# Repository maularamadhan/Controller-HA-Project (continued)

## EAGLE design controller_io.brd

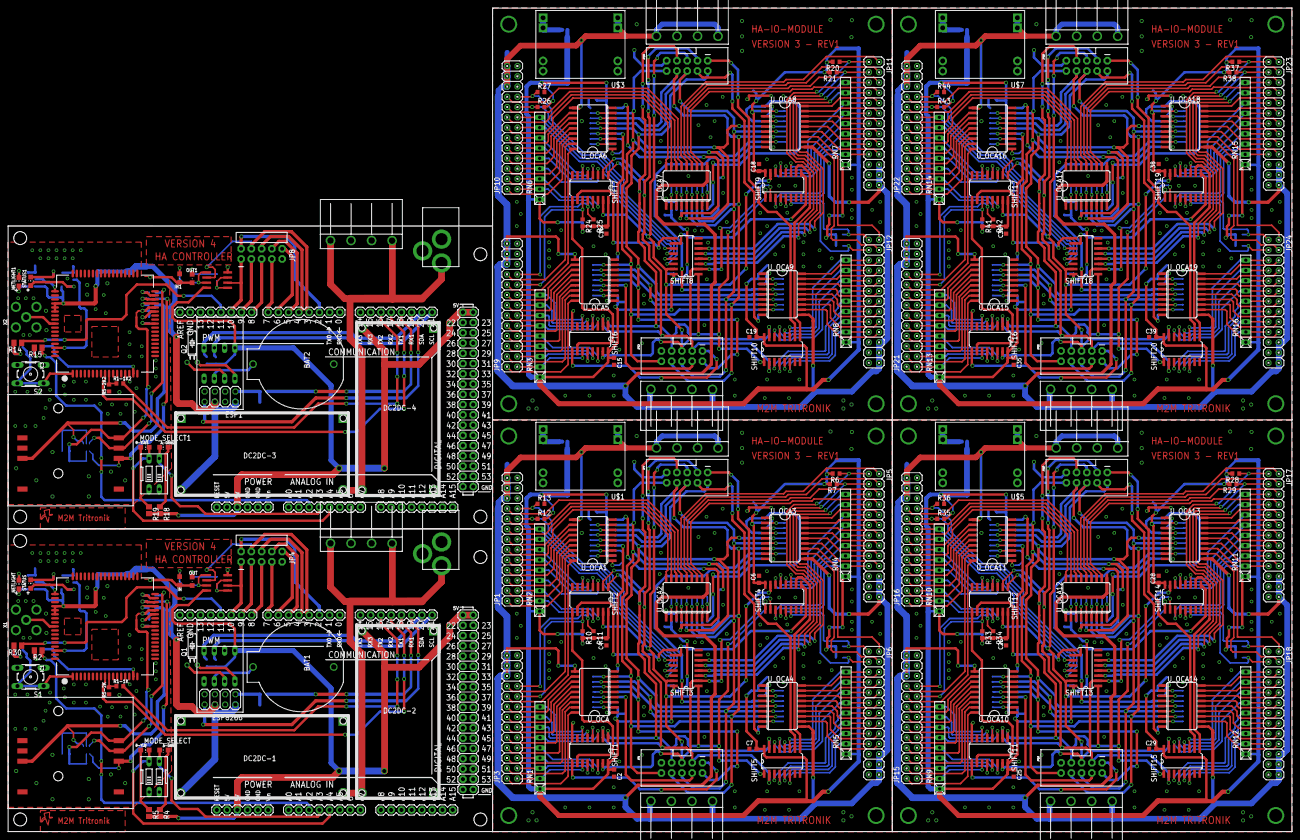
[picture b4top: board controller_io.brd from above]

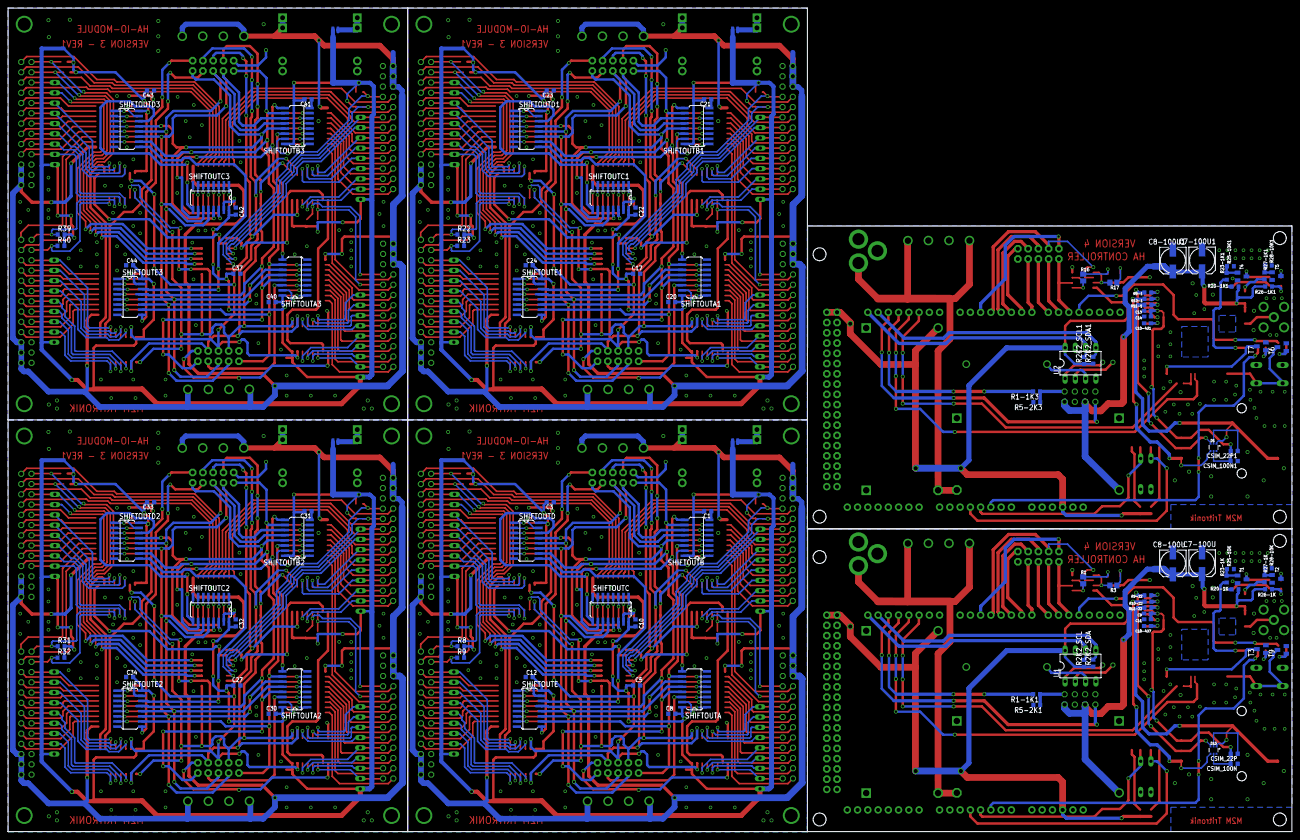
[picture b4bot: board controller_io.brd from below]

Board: 2 copper layers, 318.0 x 204.0 mm, 298 parts (112 on the bottom side), 682 nets.

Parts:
4-WAY_L-TERMINAL, 4-WAY_L-TERMINAL1: 4-PIN-CON-1759017
A-GRN, A-GRN1: green; CHIP-LED0805
ARDUINO_FOOTPRINT, ARDUINO_FOOTPRINT1: ARDUINO-MEGAFULL; ARDUINO_MEGA
B-YLW, B-YLW1: yellow; CHIP-LED0805
BAT1, BAT2: BATTCOM_20MM_PTH
C1, C2, C3, C4, C5, C6, C7, C8, C10, C12, C15, C16, C17, C18, C19, C20, C21, C22, C23, C24, C25, C26, C27, C28, C29, C30, C31, C32, C33, C34, C35, C36, C37, C38, C39, C40, C41, C42, C43, C44: 100nF; C0603K
C7-100U, C7-100U1, C8-100U, C8-100U1: 100uF; 153CLV-0605
C9, C13: 100nF; C0603
C10-4U1, C10-4U7: 4.7nF; C0603
C11, C14: 22pF; C0603
CSIM_22P, CSIM_22P1: 22pF; C0603K
CSIM_100N, CSIM_100N1: 100nF; C0603K
D1, D15: SOT363
DC2DC-1, DC2DC-2, DC2DC-3, DC2DC-4: DCDCMODULE
DC_JACKTHM, DC_JACKTHM1: 2.1MMJACKTHM; PJ-102A
ESP1, ESP8266: ESP8266
IC1, IC3: SIM900_SMT
IC2, IC4: LM358MX; SO08
IN, IN1: green; CHIPLED_0805
J1, J2, J3, J4, J5, J6, J7, J8: 4-PIN-CON-1759017
JP1, JP3, JP5, JP6, JP9, JP10, JP11, JP12, JP15, JP16, JP17, JP18, JP21, JP22, JP23, JP24: 2X13
JP2, JP7, JP13, JP14, JP19, JP20, JP25, JP26: 2X5-SHROUDED
JP4, JP8: 2X5-RA
MODE_SELECT, MODE_SELECT1: EDG-02
NETLIGHT, NETLIGHT1: green; CHIP-LED0805
OUT, OUT1: green; CHIPLED_0805
Q1, Q2: TC26H
R1, R3, R16, R17: 220; R0805
R1-1K, R1-1K1, R1-1K2, R1-1K3, R20-1K, R20-1K1, R23-1K, R23-1K1, R26-1K, R26-1K1, R27-1K, R27-1K1: 1K; R0603
R2, R14, R15, R30: 120; M0805
R2K2_SCL, R2K2_SCL1, R2K2_SDA, R2K2_SDA1: 2.2K; R0603
R4, R5, R18, R19: 1K; R0805
R5-2K, R5-2K1, R5-2K2, R5-2K3: 2K; R0603
R6, R7, R8, R9, R10, R11, R12, R13, R20, R21, R22, R23, R24, R25, R25-10K, R25-10K1, R26, R27, R28, R28-10K, R28-10K1, R29, R31, R32, R33, R34, R35, R36, R37, R38, R39, R40, R41, R42, R43, R44: 10K; R0603
R9-1, R9-22, R10-1, R10-22, R11-1, R11-22: 22; R0603
RN1, RN2, RN3, RN4, RN5, RN6, RN7, RN8, RN9, RN10, RN11, RN12, RN13, RN14, RN15, RN16: 10K; RN-9
S1, S2: B3F-10XX
SHIFT1, SHIFT2, SHIFT3, SHIFT4, SHIFT5, SHIFT6, SHIFT7, SHIFT8, SHIFT9, SHIFT10, SHIFT11, SHIFT12, SHIFT13, SHIFT14, SHIFT15, SHIFT16, SHIFT17, SHIFT18, SHIFT19, SHIFT20: 74HC165D; SO16
SHIFTOUTA, SHIFTOUTA1, SHIFTOUTA2, SHIFTOUTA3: 74HC595D; SO16
SHIFTOUTB, SHIFTOUTB1, SHIFTOUTB2, SHIFTOUTB3: 74HC595D; SO16
SHIFTOUTC, SHIFTOUTC1, SHIFTOUTC2, SHIFTOUTC3: 74HC595D; SO16
SHIFTOUTD, SHIFTOUTD1, SHIFTOUTD2, SHIFTOUTD3: 74HC595D; SO16
SHIFTOUTE, SHIFTOUTE1, SHIFTOUTE2, SHIFTOUTE3: 74HC595D; SO16
SIM_HOLDER, SIM_HOLDER1: SIM_HOLDER_PUSH
STATUS, STATUS1: yellow; CHIP-LED0805
T1, T2, T3, T4, T5, T6, T7, T9: SOT23-BEC
U1, U2: DS1307; DIL08
U$1, U$3, U$5, U$7: DCDCMODULE_SMALL; DCDCMODULE-SMALL
U$2, U$4, U$6, U$8: DOUBLE_SMALL_PAD
U_OCA, U_OCA1, U_OCA2, U_OCA3, U_OCA4, U_OCA5, U_OCA6, U_OCA7, U_OCA8, U_OCA9, U_OCA10, U_OCA11, U_OCA12, U_OCA13, U_OCA14, U_OCA15, U_OCA16, U_OCA17, U_OCA18, U_OCA19: ULN2803; SO18L
X1, X2: SMA90_DIP

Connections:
1-1: JP3.1, RN1.2, SHIFT1.11
1-2: JP3.3, RN1.3, SHIFT1.12
1-3: JP3.5, RN1.4, SHIFT1.13
1-4: JP3.7, RN1.5, SHIFT1.14
1-5: JP3.9, RN1.6, SHIFT1.3
1-6: JP3.11, RN1.7, SHIFT1.4
1-7: JP3.13, RN1.8, SHIFT1.5
1-8: JP3.15, RN1.9, SHIFT1.6
1-9: JP9.1, RN3.2, SHIFT6.11
1-10: JP9.3, RN3.3, SHIFT6.12
1-11: JP9.5, RN3.4, SHIFT6.13
1-12: JP9.7, RN3.5, SHIFT6.14
1-13: JP9.11, RN3.7, SHIFT6.4
1-14: JP9.13, RN3.8, SHIFT6.5
1-15: JP9.15, RN3.9, SHIFT6.6
1-16: JP9.9, RN3.6, SHIFT6.3
1-17: JP15.1, RN9.2, SHIFT11.11
1-18: JP15.3, RN9.3, SHIFT11.12
1-19: JP15.5, RN9.4, SHIFT11.13
1-20: JP15.7, RN9.5, SHIFT11.14
1-21: JP15.11, RN9.7, SHIFT11.4
1-22: JP15.13, RN9.8, SHIFT11.5
1-23: JP15.15, RN9.9, SHIFT11.6
1-24: JP15.9, RN9.6, SHIFT11.3
1-25: JP21.1, RN13.2, SHIFT16.11
1-26: JP21.3, RN13.3, SHIFT16.12
1-27: JP21.5, RN13.4, SHIFT16.13
1-28: JP21.7, RN13.5, SHIFT16.14
1-29: JP21.11, RN13.7, SHIFT16.4
1-30: JP21.13, RN13.8, SHIFT16.5
1-31: JP21.15, RN13.9, SHIFT16.6
1-32: JP21.9, RN13.6, SHIFT16.3
2-1: JP3.17, R10.1, SHIFT2.11
2-2: JP3.19, R11.1, SHIFT2.12
2-3: JP1.1, RN2.2, SHIFT2.13
2-4: JP1.3, RN2.3, SHIFT2.14
2-5: JP1.5, RN2.4, SHIFT2.3
2-6: JP1.7, RN2.5, SHIFT2.4
2-7: JP1.9, RN2.6, SHIFT2.5
2-8: JP1.11, RN2.7, SHIFT2.6
2-9: JP9.17, R24.1, SHIFT7.11
2-10: JP9.19, R25.1, SHIFT7.12
2-11: JP10.1, RN6.2, SHIFT7.13
2-12: JP10.3, RN6.3, SHIFT7.14
2-13: JP10.5, RN6.4, SHIFT7.3
2-14: JP10.7, RN6.5, SHIFT7.4
2-15: JP10.9, RN6.6, SHIFT7.5
2-16: JP10.11, RN6.7, SHIFT7.6
2-17: JP15.17, R33.1, SHIFT12.11
2-18: JP15.19, R34.1, SHIFT12.12
2-19: JP16.1, RN10.2, SHIFT12.13
2-20: JP16.3, RN10.3, SHIFT12.14
2-21: JP16.5, RN10.4, SHIFT12.3
2-22: JP16.7, RN10.5, SHIFT12.4
2-23: JP16.9, RN10.6, SHIFT12.5
2-24: JP16.11, RN10.7, SHIFT12.6
2-25: JP21.17, R41.1, SHIFT17.11
2-26: JP21.19, R42.1, SHIFT17.12
2-27: JP22.1, RN14.2, SHIFT17.13
2-28: JP22.3, RN14.3, SHIFT17.14
2-29: JP22.5, RN14.4, SHIFT17.3
2-30: JP22.7, RN14.5, SHIFT17.4
2-31: JP22.9, RN14.6, SHIFT17.5
2-32: JP22.11, RN14.7, SHIFT17.6
3-1: JP1.13, RN2.8, SHIFT3.11
3-2: JP1.15, RN2.9, SHIFT3.12
3-3: JP1.17, R12.1, SHIFT3.13
3-4: JP1.19, R13.1, SHIFT3.14
3-5: JP5.1, R6.1, SHIFT3.3
3-6: JP5.3, R7.1, SHIFT3.4
3-7: JP5.5, RN4.9, SHIFT3.5
3-8: JP5.7, RN4.8, SHIFT3.6
3-9: JP10.13, RN6.8, SHIFT8.11
3-10: JP10.15, RN6.9, SHIFT8.12
3-11: JP10.17, R26.1, SHIFT8.13
3-12: JP10.19, R27.1, SHIFT8.14
3-13: JP11.1, R20.1, SHIFT8.3
3-14: JP11.3, R21.1, SHIFT8.4
3-15: JP11.5, RN7.9, SHIFT8.5
3-16: JP11.7, RN7.8, SHIFT8.6
3-17: JP16.13, RN10.8, SHIFT13.11
3-18: JP16.15, RN10.9, SHIFT13.12
3-19: JP16.17, R35.1, SHIFT13.13
3-20: JP16.19, R36.1, SHIFT13.14
3-21: JP17.1, R28.1, SHIFT13.3
3-22: JP17.3, R29.1, SHIFT13.4
3-23: JP17.5, RN11.9, SHIFT13.5
3-24: JP17.7, RN11.8, SHIFT13.6
3-25: JP22.13, RN14.8, SHIFT18.11
3-26: JP22.15, RN14.9, SHIFT18.12
3-27: JP22.17, R43.1, SHIFT18.13
3-28: JP22.19, R44.1, SHIFT18.14
3-29: JP23.1, R37.1, SHIFT18.3
3-30: JP23.3, R38.1, SHIFT18.4
3-31: JP23.5, RN15.9, SHIFT18.5
3-32: JP23.7, RN15.8, SHIFT18.6
4-1: JP5.9, RN4.7, SHIFT4.11
4-2: JP5.11, RN4.6, SHIFT4.12
4-3: JP5.13, RN4.5, SHIFT4.13
4-4: JP5.15, RN4.4, SHIFT4.14
4-5: JP5.17, RN4.3, SHIFT4.3
4-6: JP5.19, RN4.2, SHIFT4.4
4-7: JP6.1, R8.1, SHIFT4.5
4-8: JP6.3, R9.1, SHIFT4.6
4-9: JP11.9, RN7.7, SHIFT9.11
4-10: JP11.11, RN7.6, SHIFT9.12
4-11: JP11.13, RN7.5, SHIFT9.13
4-12: JP11.15, RN7.4, SHIFT9.14
4-13: JP11.17, RN7.3, SHIFT9.3
4-14: JP11.19, RN7.2, SHIFT9.4
4-15: JP12.1, R22.1, SHIFT9.5
4-16: JP12.3, R23.1, SHIFT9.6
4-17: JP17.9, RN11.7, SHIFT14.11
4-18: JP17.11, RN11.6, SHIFT14.12
4-19: JP17.13, RN11.5, SHIFT14.13
4-20: JP17.15, RN11.4, SHIFT14.14
4-21: JP17.17, RN11.3, SHIFT14.3
4-22: JP17.19, RN11.2, SHIFT14.4
4-23: JP18.1, R31.1, SHIFT14.5
4-24: JP18.3, R32.1, SHIFT14.6
4-25: JP23.9, RN15.7, SHIFT19.11
4-26: JP23.11, RN15.6, SHIFT19.12
4-27: JP23.13, RN15.5, SHIFT19.13
4-28: JP23.15, RN15.4, SHIFT19.14
4-29: JP23.17, RN15.3, SHIFT19.3
4-30: JP23.19, RN15.2, SHIFT19.4
4-31: JP24.1, R39.1, SHIFT19.5
4-32: JP24.3, R40.1, SHIFT19.6
5-1: JP6.5, RN5.9, SHIFT5.11
5-2: JP6.7, RN5.8, SHIFT5.12
5-3: JP6.9, RN5.7, SHIFT5.13
5-4: JP6.11, RN5.6, SHIFT5.14
5-5: JP6.13, RN5.5, SHIFT5.3
5-6: JP6.15, RN5.4, SHIFT5.4
5-7: JP6.17, RN5.3, SHIFT5.5
5-8: JP6.19, RN5.2, SHIFT5.6
5-9: JP12.5, RN8.9, SHIFT10.11
5-10: JP12.7, RN8.8, SHIFT10.12
5-11: JP12.9, RN8.7, SHIFT10.13
5-12: JP12.11, RN8.6, SHIFT10.14
5-13: JP12.13, RN8.5, SHIFT10.3
5-14: JP12.15, RN8.4, SHIFT10.4
5-15: JP12.17, RN8.3, SHIFT10.5
5-16: JP12.19, RN8.2, SHIFT10.6
5-17: JP18.5, RN12.9, SHIFT15.11
5-18: JP18.7, RN12.8, SHIFT15.12
5-19: JP18.9, RN12.7, SHIFT15.13
5-20: JP18.11, RN12.6, SHIFT15.14
5-21: JP18.13, RN12.5, SHIFT15.3
5-22: JP18.15, RN12.4, SHIFT15.4
5-23: JP18.17, RN12.3, SHIFT15.5
5-24: JP18.19, RN12.2, SHIFT15.6
5-25: JP24.5, RN16.9, SHIFT20.11
5-26: JP24.7, RN16.8, SHIFT20.12
5-27: JP24.9, RN16.7, SHIFT20.13
5-28: JP24.11, RN16.6, SHIFT20.14
5-29: JP24.13, RN16.5, SHIFT20.3
5-30: JP24.15, RN16.4, SHIFT20.4
5-31: JP24.17, RN16.3, SHIFT20.5
5-32: JP24.19, RN16.2, SHIFT20.6
+3V1: C7-100U1.+, C8-100U1.+, DC2DC-3.VOUT, ESP1.CHPD, ESP1.VCC, IC3.P$55, IC3.P$56, IC3.P$57, R20-1K1.2, R26-1K1.2
+3V3: C7-100U.+, C8-100U.+, DC2DC-1.VOUT, ESP8266.CHPD, ESP8266.VCC, IC1.P$55, IC1.P$56, IC1.P$57, R20-1K.2, R26-1K.2
+12V: 4-WAY_L-TERMINAL.1, 4-WAY_L-TERMINAL.4, DC2DC-1.VIN, DC2DC-2.VIN, DC_JACKTHM.TIP
+12V1: J1.1, J1.4, J2.1, J2.4, JP1.22, JP1.24, JP1.26, JP3.22, JP3.24, JP3.26, JP5.22, JP5.24, JP5.26, JP6.22, JP6.24, JP6.26, U$1.INP#1, U$1.INP#2, U_OCA.10, U_OCA1.10, U_OCA2.10, U_OCA3.10, U_OCA4.10
+12V2: 4-WAY_L-TERMINAL1.1, 4-WAY_L-TERMINAL1.4, DC2DC-3.VIN, DC2DC-4.VIN, DC_JACKTHM1.TIP
+12V3: J3.1, J3.4, J4.1, J4.4, JP9.22, JP9.24, JP9.26, JP10.22, JP10.24, JP10.26, JP11.22, JP11.24, JP11.26, JP12.22, JP12.24, JP12.26, U$3.INP#1, U$3.INP#2, U_OCA5.10, U_OCA6.10, U_OCA7.10, U_OCA8.10, U_OCA9.10
+12V4: J5.1, J5.4, J6.1, J6.4, JP15.22, JP15.24, JP15.26, JP16.22, JP16.24, JP16.26, JP17.22, JP17.24, JP17.26, JP18.22, JP18.24, JP18.26, U$5.INP#1, U$5.INP#2, U_OCA10.10, U_OCA11.10, U_OCA12.10, U_OCA13.10, U_OCA14.10
+12V5: J7.1, J7.4, J8.1, J8.4, JP21.22, JP21.24, JP21.26, JP22.22, JP22.24, JP22.26, JP23.22, JP23.24, JP23.26, JP24.22, JP24.24, JP24.26, U$7.INP#1, U$7.INP#2, U_OCA15.10, U_OCA16.10, U_OCA17.10, U_OCA18.10, U_OCA19.10
A-1: SHIFTOUTA.15, U_OCA.1
A-2: SHIFTOUTA.1, U_OCA.2
A-3: SHIFTOUTA.2, U_OCA.3
A-4: SHIFTOUTA.3, U_OCA.4
A-5: SHIFTOUTA.4, U_OCA.5
A-6: SHIFTOUTA.5, U_OCA.6
A-7: SHIFTOUTA.6, U_OCA.7
A-8: SHIFTOUTA.7, U_OCA.8
A-9: SHIFTOUTA1.7, U_OCA5.8
A-10: SHIFTOUTA1.5, U_OCA5.6
A-11: SHIFTOUTA1.4, U_OCA5.5
A-12: SHIFTOUTA1.3, U_OCA5.4
A-13: SHIFTOUTA1.2, U_OCA5.3
A-14: SHIFTOUTA1.1, U_OCA5.2
A-15: SHIFTOUTA1.15, U_OCA5.1
A-16: SHIFTOUTA1.6, U_OCA5.7
A-17: SHIFTOUTA2.7, U_OCA10.8
A-18: SHIFTOUTA2.5, U_OCA10.6
A-19: SHIFTOUTA2.4, U_OCA10.5
A-20: SHIFTOUTA2.3, U_OCA10.4
A-21: SHIFTOUTA2.2, U_OCA10.3
A-22: SHIFTOUTA2.1, U_OCA10.2
A-23: SHIFTOUTA2.15, U_OCA10.1
A-24: SHIFTOUTA2.6, U_OCA10.7
A-25: SHIFTOUTA3.7, U_OCA15.8
A-26: SHIFTOUTA3.5, U_OCA15.6
A-27: SHIFTOUTA3.4, U_OCA15.5
A-28: SHIFTOUTA3.3, U_OCA15.4
A-29: SHIFTOUTA3.2, U_OCA15.3
A-30: SHIFTOUTA3.1, U_OCA15.2
A-31: SHIFTOUTA3.15, U_OCA15.1
A-32: SHIFTOUTA3.6, U_OCA15.7
B-1: SHIFTOUTB.15, U_OCA1.1
B-2: SHIFTOUTB.1, U_OCA1.2
B-3: SHIFTOUTB.2, U_OCA1.3
B-4: SHIFTOUTB.3, U_OCA1.4
B-5: SHIFTOUTB.4, U_OCA1.5
B-6: SHIFTOUTB.5, U_OCA1.6
B-7: SHIFTOUTB.6, U_OCA1.7
B-8: SHIFTOUTB.7, U_OCA1.8
B-9: SHIFTOUTB1.7, U_OCA6.8
B-10: SHIFTOUTB1.6, U_OCA6.7
B-11: SHIFTOUTB1.5, U_OCA6.6
B-12: SHIFTOUTB1.4, U_OCA6.5
B-13: SHIFTOUTB1.3, U_OCA6.4
B-14: SHIFTOUTB1.2, U_OCA6.3
B-15: SHIFTOUTB1.1, U_OCA6.2
B-16: SHIFTOUTB1.15, U_OCA6.1
B-17: SHIFTOUTB2.7, U_OCA11.8
B-18: SHIFTOUTB2.6, U_OCA11.7
B-19: SHIFTOUTB2.5, U_OCA11.6
B-20: SHIFTOUTB2.4, U_OCA11.5
B-21: SHIFTOUTB2.3, U_OCA11.4
B-22: SHIFTOUTB2.2, U_OCA11.3
B-23: SHIFTOUTB2.1, U_OCA11.2
B-24: SHIFTOUTB2.15, U_OCA11.1
B-25: SHIFTOUTB3.7, U_OCA16.8
B-26: SHIFTOUTB3.6, U_OCA16.7
B-27: SHIFTOUTB3.5, U_OCA16.6
B-28: SHIFTOUTB3.4, U_OCA16.5
B-29: SHIFTOUTB3.3, U_OCA16.4
B-30: SHIFTOUTB3.2, U_OCA16.3
B-31: SHIFTOUTB3.1, U_OCA16.2
B-32: SHIFTOUTB3.15, U_OCA16.1
C-1: SHIFTOUTC.15, U_OCA2.1
C-2: SHIFTOUTC.1, U_OCA2.2
C-3: SHIFTOUTC.2, U_OCA2.3
C-4: SHIFTOUTC.3, U_OCA2.4
C-5: SHIFTOUTC.4, U_OCA2.5
C-6: SHIFTOUTC.5, U_OCA2.6
C-7: SHIFTOUTC.6, U_OCA2.7
C-8: SHIFTOUTC.7, U_OCA2.8
C-9: SHIFTOUTC1.15, U_OCA7.1
C-10: SHIFTOUTC1.1, U_OCA7.2
C-11: SHIFTOUTC1.2, U_OCA7.3
C-12: SHIFTOUTC1.3, U_OCA7.4
C-13: SHIFTOUTC1.4, U_OCA7.5
C-14: SHIFTOUTC1.5, U_OCA7.6
C-15: SHIFTOUTC1.6, U_OCA7.7
C-16: SHIFTOUTC1.7, U_OCA7.8
C-17: SHIFTOUTC2.15, U_OCA12.1
C-18: SHIFTOUTC2.1, U_OCA12.2
C-19: SHIFTOUTC2.2, U_OCA12.3
C-20: SHIFTOUTC2.3, U_OCA12.4
C-21: SHIFTOUTC2.4, U_OCA12.5
C-22: SHIFTOUTC2.5, U_OCA12.6
C-23: SHIFTOUTC2.6, U_OCA12.7
C-24: SHIFTOUTC2.7, U_OCA12.8
C-25: SHIFTOUTC3.15, U_OCA17.1
C-26: SHIFTOUTC3.1, U_OCA17.2
C-27: SHIFTOUTC3.2, U_OCA17.3
C-28: SHIFTOUTC3.3, U_OCA17.4
C-29: SHIFTOUTC3.4, U_OCA17.5
C-30: SHIFTOUTC3.5, U_OCA17.6
C-31: SHIFTOUTC3.6, U_OCA17.7
C-32: SHIFTOUTC3.7, U_OCA17.8
CE: ARDUINO_FOOTPRINT.8, JP4.5
CE1: JP2.5, JP7.5, SHIFT1.15, SHIFT2.15, SHIFT3.15, SHIFT4.15, SHIFT5.15
CE2: ARDUINO_FOOTPRINT1.8, JP8.5
CE3: JP13.5, JP14.5, SHIFT6.15, SHIFT7.15, SHIFT8.15, SHIFT9.15, SHIFT10.15
CE4: JP19.5, JP20.5, SHIFT11.15, SHIFT12.15, SHIFT13.15, SHIFT14.15, SHIFT15.15
CE5: JP25.5, JP26.5, SHIFT16.15, SHIFT17.15, SHIFT18.15, SHIFT19.15, SHIFT20.15
CLK: ARDUINO_FOOTPRINT.9, JP4.3
CLK1: JP2.3, JP7.3, SHIFT1.2, SHIFT2.2, SHIFT3.2, SHIFT4.2, SHIFT5.2
CLK2: ARDUINO_FOOTPRINT1.9, JP8.3
CLK3: JP13.3, JP14.3, SHIFT6.2, SHIFT7.2, SHIFT8.2, SHIFT9.2, SHIFT10.2
CLK4: JP19.3, JP20.3, SHIFT11.2, SHIFT12.2, SHIFT13.2, SHIFT14.2, SHIFT15.2
CLK5: JP25.3, JP26.3, SHIFT16.2, SHIFT17.2, SHIFT18.2, SHIFT19.2, SHIFT20.2
CTRL_SIMRESET: ARDUINO_FOOTPRINT.A2, R2.1
CTRL_SIMRESET1: ARDUINO_FOOTPRINT1.A2, R15.1
D-1: SHIFTOUTD.15, U_OCA3.1
D-2: SHIFTOUTD.1, U_OCA3.2
D-3: SHIFTOUTD.2, U_OCA3.3
D-4: SHIFTOUTD.3, U_OCA3.4
D-5: SHIFTOUTD.4, U_OCA3.5
D-6: SHIFTOUTD.5, U_OCA3.6
D-7: SHIFTOUTD.6, U_OCA3.7
D-8: SHIFTOUTD.7, U_OCA3.8
D-9: SHIFTOUTD1.15, U_OCA8.1
D-10: SHIFTOUTD1.1, U_OCA8.2
D-11: SHIFTOUTD1.2, U_OCA8.3
D-12: SHIFTOUTD1.3, U_OCA8.4
D-13: SHIFTOUTD1.4, U_OCA8.5
D-14: SHIFTOUTD1.5, U_OCA8.6
D-15: SHIFTOUTD1.6, U_OCA8.7
D-16: SHIFTOUTD1.7, U_OCA8.8
D-17: SHIFTOUTD2.15, U_OCA13.1
D-18: SHIFTOUTD2.1, U_OCA13.2
D-19: SHIFTOUTD2.2, U_OCA13.3
D-20: SHIFTOUTD2.3, U_OCA13.4
D-21: SHIFTOUTD2.4, U_OCA13.5
D-22: SHIFTOUTD2.5, U_OCA13.6
D-23: SHIFTOUTD2.6, U_OCA13.7
D-24: SHIFTOUTD2.7, U_OCA13.8
D-25: SHIFTOUTD3.15, U_OCA18.1
D-26: SHIFTOUTD3.1, U_OCA18.2
D-27: SHIFTOUTD3.2, U_OCA18.3
D-28: SHIFTOUTD3.3, U_OCA18.4
D-29: SHIFTOUTD3.4, U_OCA18.5
D-30: SHIFTOUTD3.5, U_OCA18.6
D-31: SHIFTOUTD3.6, U_OCA18.7
D-32: SHIFTOUTD3.7, U_OCA18.8
E-1: SHIFTOUTE.15, U_OCA4.1
E-2: SHIFTOUTE.1, U_OCA4.2
E-3: SHIFTOUTE.2, U_OCA4.3
E-4: SHIFTOUTE.3, U_OCA4.4
E-5: SHIFTOUTE.4, U_OCA4.5
E-6: SHIFTOUTE.5, U_OCA4.6
E-7: SHIFTOUTE.6, U_OCA4.7
E-8: SHIFTOUTE.7, U_OCA4.8
E-9: SHIFTOUTE1.15, U_OCA9.1
E-10: SHIFTOUTE1.1, U_OCA9.2
E-11: SHIFTOUTE1.2, U_OCA9.3
E-12: SHIFTOUTE1.3, U_OCA9.4
E-13: SHIFTOUTE1.4, U_OCA9.5
E-14: SHIFTOUTE1.7, U_OCA9.8
E-15: SHIFTOUTE1.6, U_OCA9.7
E-16: SHIFTOUTE1.5, U_OCA9.6
E-17: SHIFTOUTE2.15, U_OCA14.1
E-18: SHIFTOUTE2.1, U_OCA14.2
E-19: SHIFTOUTE2.2, U_OCA14.3
E-20: SHIFTOUTE2.3, U_OCA14.4
E-21: SHIFTOUTE2.4, U_OCA14.5
E-22: SHIFTOUTE2.7, U_OCA14.8
E-23: SHIFTOUTE2.6, U_OCA14.7
E-24: SHIFTOUTE2.5, U_OCA14.6
E-25: SHIFTOUTE3.15, U_OCA19.1
E-26: SHIFTOUTE3.1, U_OCA19.2
E-27: SHIFTOUTE3.2, U_OCA19.3
E-28: SHIFTOUTE3.3, U_OCA19.4
E-29: SHIFTOUTE3.4, U_OCA19.5
E-30: SHIFTOUTE3.7, U_OCA19.8
E-31: SHIFTOUTE3.6, U_OCA19.7
E-32: SHIFTOUTE3.5, U_OCA19.6
ESP_RX: ESP8266.RXD, R1-1K1.1, R5-2K1.2
ESP_RX1: ESP1.RXD, R1-1K3.1, R5-2K3.2
ESP_TX: ARDUINO_FOOTPRINT.19, ESP8266.TXD
ESP_TX1: ARDUINO_FOOTPRINT1.19, ESP1.TXD
GND: 4-WAY_L-TERMINAL.2, 4-WAY_L-TERMINAL.3, ARDUINO_FOOTPRINT.GND@0, ARDUINO_FOOTPRINT.GND@1, ARDUINO_FOOTPRINT.GND@2, ARDUINO_FOOTPRINT.GND@3, ARDUINO_FOOTPRINT.GND@4, BAT1.2, C7-100U.-, C8-100U.-, C9.2, C10-4U7.2, C11.2, CSIM_22P.1, CSIM_100N.1, D15.2, DC2DC-1.GND#0, DC2DC-1.GND#1, DC2DC-2.GND#0, DC2DC-2.GND#1, DC_JACKTHM.RING, DC_JACKTHM.RING_SW, ESP8266.GND, IC1.P$17, IC1.P$18, IC1.P$29, IC1.P$39, IC1.P$45, IC1.P$46, IC1.P$53, IC1.P$54, IC1.P$58, IC1.P$59, IC1.P$61, IC1.P$62, IC1.P$63, IC1.P$64, IC1.P$65, IC2.4, IN.C, JP4.9, MODE_SELECT.1, MODE_SELECT.2, OUT.C, R5-2K.1, R5-2K1.1, R25-10K.2, R28-10K.2, S1.3, S1.4, SIM_HOLDER.GND, T1.E, T2.E, T3.E, T9.E, U1.4, X1.GND1, X1.GND2, X1.GND3, X1.GND4
GND1: C1.1, C2.1, C3.1, C4.1, C5.1, C6.1, C7.1, C8.1, C10.1, C12.1, J1.2, J1.3, J2.2, J2.3, JP1.21, JP1.23, JP1.25, JP2.9, JP3.21, JP3.23, JP3.25, JP5.21, JP5.23, JP5.25, JP6.21, JP6.23, JP6.25, JP7.9, SHIFT1.8, SHIFT2.8, SHIFT3.8, SHIFT4.8, SHIFT5.8, SHIFTOUTA.8, SHIFTOUTB.8, SHIFTOUTC.8, SHIFTOUTD.8, SHIFTOUTE.8, U$1.INM#1, U$1.INM#2, U$1.OUTM#1, U$1.OUTM#2, U_OCA.9, U_OCA1.9, U_OCA2.9, U_OCA3.9, U_OCA4.9
GND2: 4-WAY_L-TERMINAL1.2, 4-WAY_L-TERMINAL1.3, ARDUINO_FOOTPRINT1.GND@0, ARDUINO_FOOTPRINT1.GND@1, ARDUINO_FOOTPRINT1.GND@2, ARDUINO_FOOTPRINT1.GND@3, ARDUINO_FOOTPRINT1.GND@4, BAT2.2, C7-100U1.-, C8-100U1.-, C10-4U1.2, C13.2, C14.2, CSIM_22P1.1, CSIM_100N1.1, D1.2, DC2DC-3.GND#0, DC2DC-3.GND#1, DC2DC-4.GND#0, DC2DC-4.GND#1, DC_JACKTHM1.RING, DC_JACKTHM1.RING_SW, ESP1.GND, IC3.P$17, IC3.P$18, IC3.P$29, IC3.P$39, IC3.P$45, IC3.P$46, IC3.P$53, IC3.P$54, IC3.P$58, IC3.P$59, IC3.P$61, IC3.P$62, IC3.P$63, IC3.P$64, IC3.P$65, IC4.4, IN1.C, JP8.9, MODE_SELECT1.1, MODE_SELECT1.2, OUT1.C, R5-2K2.1, R5-2K3.1, R25-10K1.2, R28-10K1.2, S2.3, S2.4, SIM_HOLDER1.GND, T4.E, T5.E, T6.E, T7.E, U2.4, X2.GND1, X2.GND2, X2.GND3, X2.GND4
GND3: C15.1, C16.1, C17.1, C18.1, C19.1, C20.1, C21.1, C22.1, C23.1, C24.1, J3.2, J3.3, J4.2, J4.3, JP9.21, JP9.23, JP9.25, JP10.21, JP10.23, JP10.25, JP11.21, JP11.23, JP11.25, JP12.21, JP12.23, JP12.25, JP13.9, JP14.9, SHIFT6.8, SHIFT7.8, SHIFT8.8, SHIFT9.8, SHIFT10.8, SHIFTOUTA1.8, SHIFTOUTB1.8, SHIFTOUTC1.8, SHIFTOUTD1.8, SHIFTOUTE1.8, U$3.INM#1, U$3.INM#2, U$3.OUTM#1, U$3.OUTM#2, U_OCA5.9, U_OCA6.9, U_OCA7.9, U_OCA8.9, U_OCA9.9
GND4: C25.1, C26.1, C27.1, C28.1, C29.1, C30.1, C31.1, C32.1, C33.1, C34.1, J5.2, J5.3, J6.2, J6.3, JP15.21, JP15.23, JP15.25, JP16.21, JP16.23, JP16.25, JP17.21, JP17.23, JP17.25, JP18.21, JP18.23, JP18.25, JP19.9, JP20.9, SHIFT11.8, SHIFT12.8, SHIFT13.8, SHIFT14.8, SHIFT15.8, SHIFTOUTA2.8, SHIFTOUTB2.8, SHIFTOUTC2.8, SHIFTOUTD2.8, SHIFTOUTE2.8, U$5.INM#1, U$5.INM#2, U$5.OUTM#1, U$5.OUTM#2, U_OCA10.9, U_OCA11.9, U_OCA12.9, U_OCA13.9, U_OCA14.9
GND5: C35.1, C36.1, C37.1, C38.1, C39.1, C40.1, C41.1, C42.1, C43.1, C44.1, J7.2, J7.3, J8.2, J8.3, JP21.21, JP21.23, JP21.25, JP22.21, JP22.23, JP22.25, JP23.21, JP23.23, JP23.25, JP24.21, JP24.23, JP24.25, JP25.9, JP26.9, SHIFT16.8, SHIFT17.8, SHIFT18.8, SHIFT19.8, SHIFT20.8, SHIFTOUTA3.8, SHIFTOUTB3.8, SHIFTOUTC3.8, SHIFTOUTD3.8, SHIFTOUTE3.8, U$7.INM#1, U$7.INM#2, U$7.OUTM#1, U$7.OUTM#2, U_OCA15.9, U_OCA16.9, U_OCA17.9, U_OCA18.9, U_OCA19.9
MR: ARDUINO_FOOTPRINT.6, JP4.10
MR1: JP2.10, JP7.10, SHIFTOUTA.10, SHIFTOUTB.10, SHIFTOUTC.10, SHIFTOUTD.10, SHIFTOUTE.10
MR2: ARDUINO_FOOTPRINT1.6, JP8.10
MR3: JP13.10, JP14.10, SHIFTOUTA1.10, SHIFTOUTB1.10, SHIFTOUTC1.10, SHIFTOUTD1.10, SHIFTOUTE1.10
MR4: JP19.10, JP20.10, SHIFTOUTA2.10, SHIFTOUTB2.10, SHIFTOUTC2.10, SHIFTOUTD2.10, SHIFTOUTE2.10
MR5: JP25.10, JP26.10, SHIFTOUTA3.10, SHIFTOUTB3.10, SHIFTOUTC3.10, SHIFTOUTD3.10, SHIFTOUTE3.10
unnamed: ARDUINO_FOOTPRINT.16, R1-1K.2
unnamed: IC1.P$31, R11-22.1
unnamed: IC1.P$32, R10-22.1
unnamed: IC1.P$33, R9-22.1
unnamed: C10-4U7.1, IC1.P$26
unnamed: IC1.P$60, X1.ANTENNA
unnamed: R20-1K.1, STATUS.A
unnamed: STATUS.C, T1.C
unnamed: R23-1K.1, R25-10K.1, T1.B
unnamed: NETLIGHT.A, R26-1K.1
unnamed: NETLIGHT.C, T2.C
unnamed: R27-1K.1, R28-10K.1, T2.B
unnamed: R30.2, T9.B
unnamed: R2.2, T3.B
unnamed: Q1.1, U1.2
unnamed: Q1.2, U1.1
unnamed: ARDUINO_FOOTPRINT.18, R1-1K1.2
unnamed: IC2.1, IC2.3, R1.1
unnamed: BAT1.1, U1.3
unnamed: IC2.5, IC2.7, R3.1
unnamed: OUT.A, R1.2
unnamed: IN.A, R3.2
unnamed: A-GRN.A, R4.1
unnamed: B-YLW.A, R5.1
unnamed: SHIFT2.10, SHIFT3.9
unnamed: SHIFT3.10, SHIFT4.9
unnamed: SHIFT4.10, SHIFT5.9
unnamed: SHIFTOUTA.9, SHIFTOUTB.14
unnamed: SHIFTOUTC.9, SHIFTOUTD.14
unnamed: SHIFTOUTB.9, SHIFTOUTC.14
unnamed: SHIFTOUTD.9, SHIFTOUTE.14
unnamed: U$1.OUTP#1, U$1.OUTP#2, U$2.PAD1
unnamed: IC3.P$31, R11-1.1
unnamed: IC3.P$32, R10-1.1
unnamed: IC3.P$33, R9-1.1
unnamed: C10-4U1.1, IC3.P$26
unnamed: IC3.P$60, X2.ANTENNA
unnamed: SHIFT1.10, SHIFT2.9
unnamed: R20-1K1.1, STATUS1.A
unnamed: STATUS1.C, T4.C
unnamed: R23-1K1.1, R25-10K1.1, T4.B
unnamed: NETLIGHT1.A, R26-1K1.1
unnamed: NETLIGHT1.C, T5.C
unnamed: R27-1K1.1, R28-10K1.1, T5.B
unnamed: R14.2, T6.B
unnamed: R15.2, T7.B
unnamed: BAT2.1, U2.3
unnamed: Q2.1, U2.2
unnamed: Q2.2, U2.1
unnamed: IC4.1, IC4.3, R16.1
unnamed: IC4.5, IC4.7, R17.1
unnamed: OUT1.A, R16.2
unnamed: IN1.A, R17.2
unnamed: A-GRN1.A, R18.1
unnamed: B-YLW1.A, R19.1
unnamed: ARDUINO_FOOTPRINT1.18, R1-1K3.2
unnamed: ARDUINO_FOOTPRINT1.16, R1-1K2.2
unnamed: SHIFT6.10, SHIFT7.9
unnamed: SHIFT7.10, SHIFT8.9
unnamed: SHIFT8.10, SHIFT9.9
unnamed: SHIFT9.10, SHIFT10.9
unnamed: SHIFTOUTA1.9, SHIFTOUTB1.14
unnamed: SHIFTOUTC1.9, SHIFTOUTD1.14
unnamed: SHIFTOUTB1.9, SHIFTOUTC1.14
unnamed: SHIFTOUTD1.9, SHIFTOUTE1.14
unnamed: U$3.OUTP#1, U$3.OUTP#2, U$4.PAD1
unnamed: SHIFT11.10, SHIFT12.9
unnamed: SHIFT12.10, SHIFT13.9
unnamed: SHIFT13.10, SHIFT14.9
unnamed: SHIFT14.10, SHIFT15.9
unnamed: SHIFTOUTA2.9, SHIFTOUTB2.14
unnamed: SHIFTOUTC2.9, SHIFTOUTD2.14
unnamed: SHIFTOUTB2.9, SHIFTOUTC2.14
unnamed: SHIFTOUTD2.9, SHIFTOUTE2.14
unnamed: U$5.OUTP#1, U$5.OUTP#2, U$6.PAD1
unnamed: SHIFT16.10, SHIFT17.9
unnamed: SHIFT17.10, SHIFT18.9
unnamed: SHIFT18.10, SHIFT19.9
unnamed: SHIFT19.10, SHIFT20.9
unnamed: SHIFTOUTA3.9, SHIFTOUTB3.14
unnamed: SHIFTOUTC3.9, SHIFTOUTD3.14
unnamed: SHIFTOUTB3.9, SHIFTOUTC3.14
unnamed: SHIFTOUTD3.9, SHIFTOUTE3.14
unnamed: U$7.OUTP#1, U$7.OUTP#2, U$8.PAD1
OE: ARDUINO_FOOTPRINT.2, JP4.2
OE1: JP2.2, JP7.2, SHIFTOUTA.13, SHIFTOUTB.13, SHIFTOUTC.13, SHIFTOUTD.13, SHIFTOUTE.13
OE2: ARDUINO_FOOTPRINT1.2, JP8.2
OE3: JP13.2, JP14.2, SHIFTOUTA1.13, SHIFTOUTB1.13, SHIFTOUTC1.13, SHIFTOUTD1.13, SHIFTOUTE1.13
OE4: JP19.2, JP20.2, SHIFTOUTA2.13, SHIFTOUTB2.13, SHIFTOUTC2.13, SHIFTOUTD2.13, SHIFTOUTE2.13
OE5: JP25.2, JP26.2, SHIFTOUTA3.13, SHIFTOUTB3.13, SHIFTOUTC3.13, SHIFTOUTD3.13, SHIFTOUTE3.13
OUTA1: JP3.2, U_OCA.18
OUTA2: JP3.4, U_OCA.17
OUTA3: JP3.6, U_OCA.16
OUTA4: JP3.8, U_OCA.15
OUTA5: JP3.10, U_OCA.14
OUTA6: JP3.12, U_OCA.13
OUTA7: JP3.14, U_OCA.12
OUTA8: JP3.16, U_OCA.11
OUTA9: JP9.2, U_OCA5.18
OUTA10: JP9.4, U_OCA5.17
OUTA11: JP9.6, U_OCA5.16
OUTA12: JP9.8, U_OCA5.15
OUTA13: JP9.10, U_OCA5.14
OUTA14: JP9.12, U_OCA5.13
OUTA15: JP9.14, U_OCA5.12
OUTA16: JP9.16, U_OCA5.11
OUTA17: JP15.2, U_OCA10.18
OUTA18: JP15.4, U_OCA10.17
OUTA19: JP15.6, U_OCA10.16
OUTA20: JP15.8, U_OCA10.15
OUTA21: JP15.10, U_OCA10.14
OUTA22: JP15.12, U_OCA10.13
OUTA23: JP15.14, U_OCA10.12
OUTA24: JP15.16, U_OCA10.11
OUTA25: JP21.2, U_OCA15.18
OUTA26: JP21.4, U_OCA15.17
OUTA27: JP21.6, U_OCA15.16
OUTA28: JP21.8, U_OCA15.15
OUTA29: JP21.10, U_OCA15.14
OUTA30: JP21.12, U_OCA15.13
OUTA31: JP21.14, U_OCA15.12
OUTA32: JP21.16, U_OCA15.11
OUTB1: JP3.18, U_OCA1.18
OUTB2: JP3.20, U_OCA1.17
OUTB3: JP1.2, U_OCA1.16
OUTB4: JP1.4, U_OCA1.15
OUTB5: JP1.6, U_OCA1.14
OUTB6: JP1.8, U_OCA1.13
OUTB7: JP1.10, U_OCA1.12
OUTB8: JP1.12, U_OCA1.11
OUTB9: JP9.18, U_OCA6.18
OUTB10: JP9.20, U_OCA6.17
OUTB11: JP10.2, U_OCA6.16
OUTB12: JP10.4, U_OCA6.15
OUTB13: JP10.6, U_OCA6.14
OUTB14: JP10.8, U_OCA6.13
OUTB15: JP10.10, U_OCA6.12
OUTB16: JP10.12, U_OCA6.11
OUTB17: JP15.18, U_OCA11.18
OUTB18: JP15.20, U_OCA11.17
OUTB19: JP16.2, U_OCA11.16
OUTB20: JP16.4, U_OCA11.15
OUTB21: JP16.6, U_OCA11.14
OUTB22: JP16.8, U_OCA11.13
OUTB23: JP16.10, U_OCA11.12
OUTB24: JP16.12, U_OCA11.11
OUTB25: JP21.18, U_OCA16.18
OUTB26: JP21.20, U_OCA16.17
OUTB27: JP22.2, U_OCA16.16
OUTB28: JP22.4, U_OCA16.15
OUTB29: JP22.6, U_OCA16.14
OUTB30: JP22.8, U_OCA16.13
OUTB31: JP22.10, U_OCA16.12
OUTB32: JP22.12, U_OCA16.11
OUTC1: JP1.14, U_OCA2.18
OUTC2: JP1.16, U_OCA2.17
OUTC3: JP1.18, U_OCA2.16
OUTC4: JP1.20, U_OCA2.15
OUTC5: JP5.2, U_OCA2.14
OUTC6: JP5.4, U_OCA2.13
OUTC7: JP5.6, U_OCA2.12
OUTC8: JP5.8, U_OCA2.11
OUTC9: JP10.14, U_OCA7.18
OUTC10: JP10.16, U_OCA7.17
OUTC11: JP10.18, U_OCA7.16
OUTC12: JP10.20, U_OCA7.15
OUTC13: JP11.2, U_OCA7.14
OUTC14: JP11.4, U_OCA7.13
OUTC15: JP11.6, U_OCA7.12
OUTC16: JP11.8, U_OCA7.11
OUTC17: JP16.14, U_OCA12.18
OUTC18: JP16.16, U_OCA12.17
OUTC19: JP16.18, U_OCA12.16
OUTC20: JP16.20, U_OCA12.15
OUTC21: JP17.2, U_OCA12.14
OUTC22: JP17.4, U_OCA12.13
OUTC23: JP17.6, U_OCA12.12
OUTC24: JP17.8, U_OCA12.11
OUTC25: JP22.14, U_OCA17.18
OUTC26: JP22.16, U_OCA17.17
OUTC27: JP22.18, U_OCA17.16
OUTC28: JP22.20, U_OCA17.15
OUTC29: JP23.2, U_OCA17.14
OUTC30: JP23.4, U_OCA17.13
OUTC31: JP23.6, U_OCA17.12
OUTC32: JP23.8, U_OCA17.11
OUTD1: JP5.10, U_OCA3.18
OUTD2: JP5.12, U_OCA3.17
OUTD3: JP5.14, U_OCA3.16
OUTD4: JP5.16, U_OCA3.15
OUTD5: JP5.18, U_OCA3.14
OUTD6: JP5.20, U_OCA3.13
OUTD7: JP6.2, U_OCA3.12
OUTD8: JP6.4, U_OCA3.11
OUTD9: JP11.10, U_OCA8.18
OUTD10: JP11.12, U_OCA8.17
OUTD11: JP11.14, U_OCA8.16
OUTD12: JP11.16, U_OCA8.15
OUTD13: JP11.18, U_OCA8.14
OUTD14: JP11.20, U_OCA8.13
OUTD15: JP12.2, U_OCA8.12
OUTD16: JP12.4, U_OCA8.11
OUTD17: JP17.10, U_OCA13.18
OUTD18: JP17.12, U_OCA13.17
OUTD19: JP17.14, U_OCA13.16
OUTD20: JP17.16, U_OCA13.15
OUTD21: JP17.18, U_OCA13.14
OUTD22: JP17.20, U_OCA13.13
OUTD23: JP18.2, U_OCA13.12
OUTD24: JP18.4, U_OCA13.11
OUTD25: JP23.10, U_OCA18.18
OUTD26: JP23.12, U_OCA18.17
OUTD27: JP23.14, U_OCA18.16
OUTD28: JP23.16, U_OCA18.15
OUTD29: JP23.18, U_OCA18.14
OUTD30: JP23.20, U_OCA18.13
OUTD31: JP24.2, U_OCA18.12
OUTD32: JP24.4, U_OCA18.11
OUTE1: JP6.6, U_OCA4.18
OUTE2: JP6.8, U_OCA4.17
OUTE3: JP6.10, U_OCA4.16
OUTE4: JP6.12, U_OCA4.15
OUTE5: JP6.14, U_OCA4.14
OUTE6: JP6.16, U_OCA4.13
OUTE7: JP6.18, U_OCA4.12
OUTE8: JP6.20, U_OCA4.11
OUTE9: JP12.6, U_OCA9.18
OUTE10: JP12.10, U_OCA9.16
OUTE11: JP12.8, U_OCA9.17
OUTE12: JP12.12, U_OCA9.15
OUTE13: JP12.14, U_OCA9.14
OUTE14: JP12.16, U_OCA9.13
OUTE15: JP12.18, U_OCA9.12
OUTE16: JP12.20, U_OCA9.11
OUTE17: JP18.6, U_OCA14.18
OUTE18: JP18.10, U_OCA14.16
OUTE19: JP18.8, U_OCA14.17
OUTE20: JP18.12, U_OCA14.15
OUTE21: JP18.14, U_OCA14.14
OUTE22: JP18.16, U_OCA14.13
OUTE23: JP18.18, U_OCA14.12
OUTE24: JP18.20, U_OCA14.11
OUTE25: JP24.6, U_OCA19.18
OUTE26: JP24.10, U_OCA19.16
OUTE27: JP24.8, U_OCA19.17
OUTE28: JP24.12, U_OCA19.15
OUTE29: JP24.14, U_OCA19.14
OUTE30: JP24.16, U_OCA19.13
OUTE31: JP24.18, U_OCA19.12
OUTE32: JP24.20, U_OCA19.11
PL: ARDUINO_FOOTPRINT.7, JP4.7
PL1: JP2.7, JP7.7, SHIFT1.1, SHIFT2.1, SHIFT3.1, SHIFT4.1, SHIFT5.1
PL2: ARDUINO_FOOTPRINT1.7, JP8.7
PL3: JP13.7, JP14.7, SHIFT6.1, SHIFT7.1, SHIFT8.1, SHIFT9.1, SHIFT10.1
PL4: JP19.7, JP20.7, SHIFT11.1, SHIFT12.1, SHIFT13.1, SHIFT14.1, SHIFT15.1
PL5: JP25.7, JP26.7, SHIFT16.1, SHIFT17.1, SHIFT18.1, SHIFT19.1, SHIFT20.1
PWRKEY: ARDUINO_FOOTPRINT.11, R30.1
PWRKEY1: ARDUINO_FOOTPRINT1.11, R14.1
Q1: JP2.1, SHIFT1.9
Q2: ARDUINO_FOOTPRINT1.10, IC4.2, JP8.1
Q3: JP13.1, SHIFT6.9
Q4: JP19.1, SHIFT11.9
Q5: JP25.1, SHIFT16.9
Q7: ARDUINO_FOOTPRINT.10, IC2.2, JP4.1
Q7_1: JP14.1, SHIFT10.10
Q7_2: JP7.1, SHIFT5.10
Q7_3: JP20.1, SHIFT15.10
Q7_4: JP26.1, SHIFT20.10
SCL: ARDUINO_FOOTPRINT.21, R2K2_SCL.2, U1.6
SCL1: ARDUINO_FOOTPRINT1.21, R2K2_SCL1.2, U2.6
SDA: ARDUINO_FOOTPRINT.20, R2K2_SDA.2, U1.5
SDA1: ARDUINO_FOOTPRINT1.20, R2K2_SDA1.2, U2.5
SHCP: ARDUINO_FOOTPRINT.5, JP4.8
SHCP1: JP2.8, JP7.8, SHIFTOUTA.11, SHIFTOUTB.11, SHIFTOUTC.11, SHIFTOUTD.11, SHIFTOUTE.11
SHCP2: ARDUINO_FOOTPRINT1.5, JP8.8
SHCP3: JP13.8, JP14.8, SHIFTOUTA1.11, SHIFTOUTB1.11, SHIFTOUTC1.11, SHIFTOUTD1.11, SHIFTOUTE1.11
SHCP4: JP19.8, JP20.8, SHIFTOUTA2.11, SHIFTOUTB2.11, SHIFTOUTC2.11, SHIFTOUTD2.11, SHIFTOUTE2.11
SHCP5: JP25.8, JP26.8, SHIFTOUTA3.11, SHIFTOUTB3.11, SHIFTOUTC3.11, SHIFTOUTD3.11, SHIFTOUTE3.11
SIM_NETLIGHT: IC1.P$52, R27-1K.2
SIM_NETLIGHT1: IC3.P$52, R27-1K1.2
SIM_PWRKEY: IC1.P$1, S1.1, S1.2, T9.C
SIM_PWRKEY1: IC3.P$1, S2.1, S2.2, T6.C
SIM_RESET: IC1.P$16, T3.C
SIM_RESET1: IC3.P$16, T7.C
SIM_RX: IC1.P$10, R1-1K.1, R5-2K.2
SIM_RX1: IC3.P$10, R1-1K2.1, R5-2K2.2
SIM_STATUS: IC1.P$66, R23-1K.2
SIM_STATUS1: IC3.P$66, R23-1K1.2
SIM_TX: ARDUINO_FOOTPRINT.17, IC1.P$9
SIM_TX1: ARDUINO_FOOTPRINT1.17, IC3.P$9
SR_DS: ARDUINO_FOOTPRINT.3, IC2.6, JP4.4
SR_DS1: JP2.4, SHIFTOUTA.14
SR_DS2: ARDUINO_FOOTPRINT1.3, IC4.6, JP8.4
SR_DS3: JP13.4, SHIFTOUTA1.14
SR_DS4: JP19.4, SHIFTOUTA2.14
SR_DS5: JP25.4, SHIFTOUTA3.14
SR_DS_1: JP14.4, SHIFTOUTE1.9
SR_DS_2: JP7.4, SHIFTOUTE.9
SR_DS_3: JP20.4, SHIFTOUTE2.9
SR_DS_4: JP26.4, SHIFTOUTE3.9
STATE_A: A-GRN.C, ARDUINO_FOOTPRINT.A3, MODE_SELECT.3
STATE_A1: A-GRN1.C, ARDUINO_FOOTPRINT1.A3, MODE_SELECT1.3
STATE_B: ARDUINO_FOOTPRINT.A4, B-YLW.C, MODE_SELECT.4
STATE_B1: ARDUINO_FOOTPRINT1.A4, B-YLW1.C, MODE_SELECT1.4
STCP: ARDUINO_FOOTPRINT.4, JP4.6
STCP1: JP2.6, JP7.6, SHIFTOUTA.12, SHIFTOUTB.12, SHIFTOUTC.12, SHIFTOUTD.12, SHIFTOUTE.12
STCP2: ARDUINO_FOOTPRINT1.4, JP8.6
STCP3: JP13.6, JP14.6, SHIFTOUTA1.12, SHIFTOUTB1.12, SHIFTOUTC1.12, SHIFTOUTD1.12, SHIFTOUTE1.12
STCP4: JP19.6, JP20.6, SHIFTOUTA2.12, SHIFTOUTB2.12, SHIFTOUTC2.12, SHIFTOUTD2.12, SHIFTOUTE2.12
STCP5: JP25.6, JP26.6, SHIFTOUTA3.12, SHIFTOUTB3.12, SHIFTOUTC3.12, SHIFTOUTD3.12, SHIFTOUTE3.12
USIM_CLK: D15.4, R10-22.2, SIM_HOLDER.CLK
USIM_CLK1: D1.4, R10-1.2, SIM_HOLDER1.CLK
USIM_DATA: D15.1, R11-22.2, SIM_HOLDER.I/O
USIM_DATA1: D1.1, R11-1.2, SIM_HOLDER1.I/O
USIM_RESET: D15.3, R9-22.2, SIM_HOLDER.RST
USIM_RESET1: D1.3, R9-1.2, SIM_HOLDER1.RST
USIM_VCC: C9.1, C11.1, CSIM_22P.2, CSIM_100N.2, D15.5, IC1.P$30, SIM_HOLDER.VCC
USIM_VCC1: C13.1, C14.1, CSIM_22P1.2, CSIM_100N1.2, D1.5, IC3.P$30, SIM_HOLDER1.VCC
VCC: ARDUINO_FOOTPRINT.5V@0, ARDUINO_FOOTPRINT.5V@1, ARDUINO_FOOTPRINT.5V@2, DC2DC-2.VOUT, IC2.8, R2K2_SCL.1, R2K2_SDA.1, R4.2, R5.2, U1.8
VCC1: C1.2, C2.2, C3.2, C4.2, C5.2, C6.2, C7.2, C8.2, C10.2, C12.2, R6.2, R7.2, R8.2, R9.2, R10.2, R11.2, R12.2, R13.2, RN1.1, RN2.1, RN4.1, RN5.1, SHIFT1.16, SHIFT2.16, SHIFT3.16, SHIFT4.16, SHIFT5.16, SHIFTOUTA.16, SHIFTOUTB.16, SHIFTOUTC.16, SHIFTOUTD.16, SHIFTOUTE.16, U$2.PAD2
VCC2: ARDUINO_FOOTPRINT1.5V@0, ARDUINO_FOOTPRINT1.5V@1, ARDUINO_FOOTPRINT1.5V@2, DC2DC-4.VOUT, IC4.8, R2K2_SCL1.1, R2K2_SDA1.1, R18.2, R19.2, U2.8
VCC3: C15.2, C16.2, C17.2, C18.2, C19.2, C20.2, C21.2, C22.2, C23.2, C24.2, R20.2, R21.2, R22.2, R23.2, R24.2, R25.2, R26.2, R27.2, RN3.1, RN6.1, RN7.1, RN8.1, SHIFT6.16, SHIFT7.16, SHIFT8.16, SHIFT9.16, SHIFT10.16, SHIFTOUTA1.16, SHIFTOUTB1.16, SHIFTOUTC1.16, SHIFTOUTD1.16, SHIFTOUTE1.16, U$4.PAD2
VCC4: C25.2, C26.2, C27.2, C28.2, C29.2, C30.2, C31.2, C32.2, C33.2, C34.2, R28.2, R29.2, R31.2, R32.2, R33.2, R34.2, R35.2, R36.2, RN9.1, RN10.1, RN11.1, RN12.1, SHIFT11.16, SHIFT12.16, SHIFT13.16, SHIFT14.16, SHIFT15.16, SHIFTOUTA2.16, SHIFTOUTB2.16, SHIFTOUTC2.16, SHIFTOUTD2.16, SHIFTOUTE2.16, U$6.PAD2
VCC5: C35.2, C36.2, C37.2, C38.2, C39.2, C40.2, C41.2, C42.2, C43.2, C44.2, R37.2, R38.2, R39.2, R40.2, R41.2, R42.2, R43.2, R44.2, RN13.1, RN14.1, RN15.1, RN16.1, SHIFT16.16, SHIFT17.16, SHIFT18.16, SHIFT19.16, SHIFT20.16, SHIFTOUTA3.16, SHIFTOUTB3.16, SHIFTOUTC3.16, SHIFTOUTD3.16, SHIFTOUTE3.16, U$8.PAD2

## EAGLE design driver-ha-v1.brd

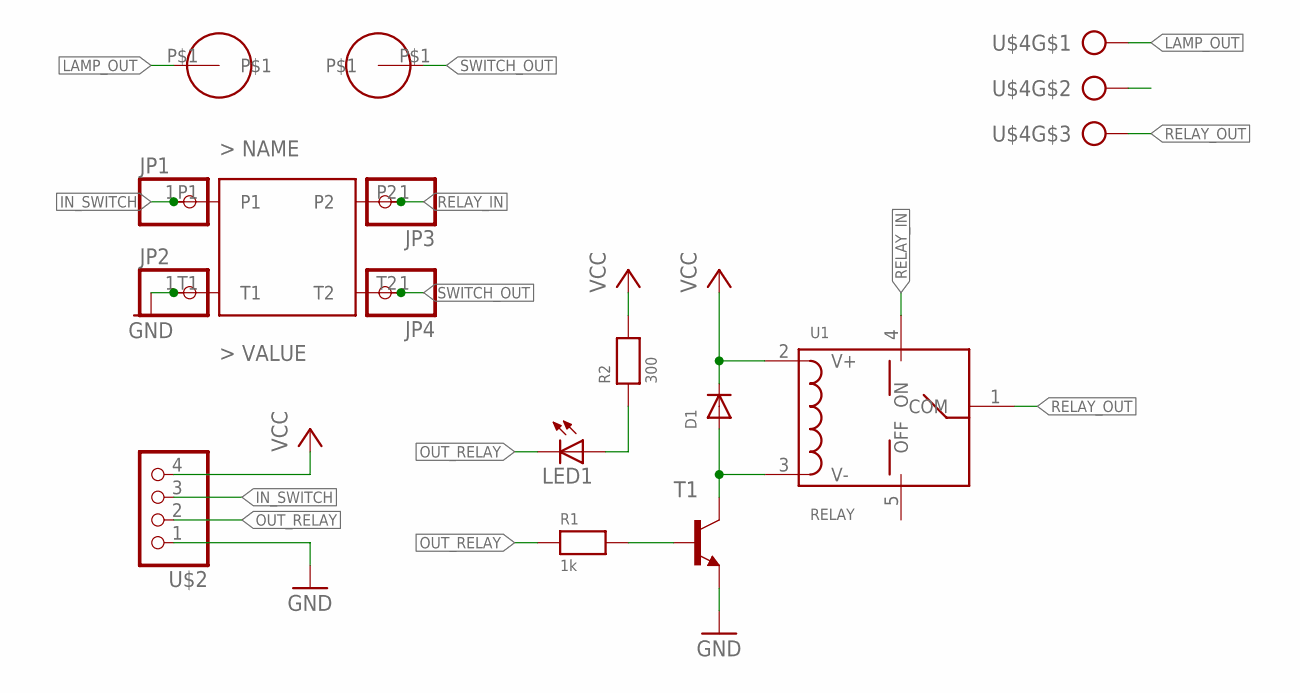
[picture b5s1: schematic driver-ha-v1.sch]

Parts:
D1: DIODESMA; SMADIODE
JP1, JP2, JP3, JP4: PINHD-1X1; 1X01
LED1: LEDCHIPLED_0805; CHIPLED_0805
R1: 1k; 0603
R2: 300; 0603
ROOM_SWITCH: DPST-SWITCH-1221; TOGGLE-SW-E1221
T1: MMBT2222ALT1-NPN-SOT23-BEC; SOT23-BEC
U1: RELAY
U$1, U$3: CONN-CABLE
U$2: HEADER-1X4; 1X04_OVAL
U$4: AK3003

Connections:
GND: JP2.1, ROOM_SWITCH.T1, T1.E, U$2.1
IN_SWITCH: JP1.1, ROOM_SWITCH.P1, U$2.3
LAMP_OUT: U$1.P$1, U$4.1
unnamed: R1.2, T1.B
unnamed: LED1.A, R2.1
unnamed: D1.A, T1.C, U1.3 (V-)
OUT_RELAY: LED1.C, R1.1, U$2.2
RELAY_IN: JP3.1, ROOM_SWITCH.P2, U1.4 (ON)
RELAY_OUT: U1.1 (COM), U$4.3
SWITCH_OUT: JP4.1, ROOM_SWITCH.T2, U$3.P$1
VCC: D1.C, R2.2, U1.2 (V+), U$2.4

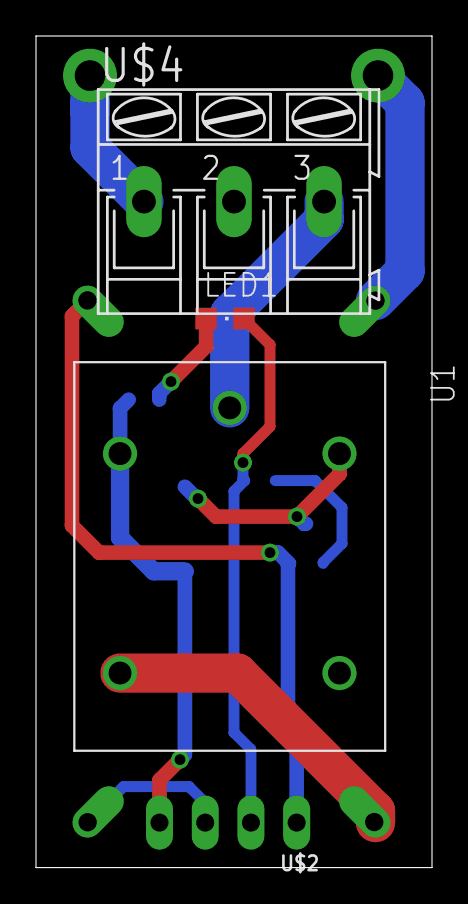
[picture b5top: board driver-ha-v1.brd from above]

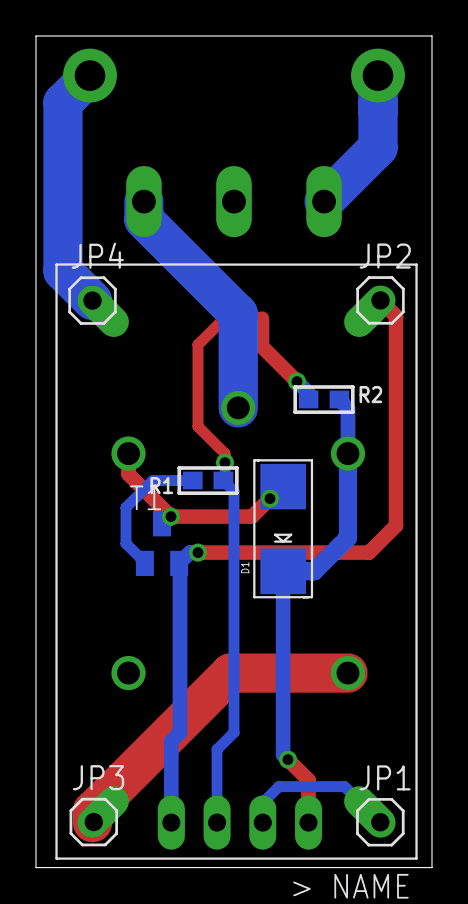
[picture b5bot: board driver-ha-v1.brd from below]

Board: 2 copper layers, 22.0 x 46.2 mm, 15 parts (9 on the bottom side), 11 nets.
